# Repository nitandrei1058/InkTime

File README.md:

# InkTime - Smartwatch Open Source

## Diagrama Bloc

```mermaid
graph TD
    subgraph Power Management
        J4[USB-C Connector] -->|VBUS| D3[USBLC6-2SC6Y ESD]
        D3 --> IC1[BQ25180 LiPo Charger]
        BATT[LiPo Battery 250mAh] <--> IC1
        BATT --> U3[MAX17048 Fuel Gauge]
        IC1 -->|VSYS| IC9[RT6160A DC-DC Buck-Boost]
        IC9 -->|3.3V| VDD_SYS[System 3.3V]
    end

    subgraph Microcontroller
        U1[nRF52840 SoC]
        VDD_SYS --> U1
        U1 <-->|SWD| J2[TC2030 Debug]
        U1 <-->|RF| ANT[2.4GHz Antenna]
    end

    subgraph Peripherals
        U1 -->|I2C| IC3[BMA421 IMU]
        U1 -->|I2C| U3
        U1 -->|I2C| IC2[DRV2605L Haptic]
        U1 -->|I2C| IC1
        IC2 --> MOTOR[Vibration Motor]
        U1 -->|SPI + GPIO| J1["EPD Display 1.54 inch"]
        U1 -->|GPIO| BTN[3x Tactile Buttons]
    end
```

## Bill of Materials (BOM)

| Referință | Componentă | Valoare / Pachet | Datasheet | Link JLCParts / Procurare |
|:---|:---|:---|:---|:---|
| **U1** | Nordic nRF52840 | nRF52840-QIAA (QFN-73) | [Datasheet](https://infocenter.nordicsemi.com/pdf/nRF52840_PS_v1.7.pdf) | [C190794](https://jlcpcb.com/partdetail/NordicSemiconductor-nRF52840QIAA/C190794) |
| **IC1** | TI BQ25180 | LiPo Charger (DSBGA-8) | [Datasheet](https://www.ti.com/lit/ds/symlink/bq25180.pdf) | [C3682423](https://jlcpcb.com/partdetail/TexasInstruments-BQ25180YBGR/C3682423) |
| **IC9** | Richtek RT6160A | DC-DC Buck-Boost 3.3V | [Datasheet](https://www.richtek.com/assets/product_file/RT6160A/DS6160A-00.pdf) | [C7065276](https://jlcpcb.com/partdetail/RichtekTech-RT6160AWSC/C7065276) |
| **U3** | Analog MAX17048 | Fuel Gauge (TDFN-8) | [Datasheet](https://www.analog.com/media/en/technical-documentation/data-sheets/MAX17048-MAX17049.pdf) | [C2682616](https://jlcpcb.com/partdetail/2777647-MAX17048GT10/C2682616) |
| **IC3** | Bosch BMA421 | Accelerometru (LGA-12) | [Datasheet](https://www.bosch-sensortec.com/media/boschsensortec/downloads/datasheets/bst-bma423-ds000.pdf) | [C5242966](https://jlcpcb.com/partdetail/BoschSensortec-BMA423/C189517) |
| **IC2** | TI DRV2605L | Haptic Driver (DSBGA) | [Datasheet](https://www.ti.com/lit/ds/symlink/drv2605.pdf) | [C527464](https://jlcpcb.com/partdetail/TexasInstruments-DRV2605YZFR/C81079) |
| **D3** | ST USBLC6-2SC6Y | USB ESD (SOT-23-6) | [Datasheet](https://www.st.com/resource/en/datasheet/usblc6-2.pdf) | [C2969755](https://jlcpcb.com/partdetail/STMicroelectronics-USBLC62SC6Y/C2969755) |
| **J4** | KH-TYPE-C-16P | USB-C 16-pin | - | [C709357](https://jlcpcb.com/partdetail/Shenzhen_KinghelmElec-KH_TYPE_C16P/C709357) |
| **J1** | Molex 503480-2400 | FPC 24-pin pt EPD | [Datasheet](https://www.molex.com/en-us/products/part-detail/503480-2400) | [C122434](https://jlcpcb.com/partdetail/MOLEX-5034802400/C122434) |
| **J2** | TC2030-IDC | SWD Tag-Connect | [Datasheet](https://www.tag-connect.com/product/tc2030-idc-nl) | - |
| **ANT1**| Johanson 2450AT18 | Antenă 2.4GHz | [Datasheet](https://www.johansontechnology.com/datasheets/2450AT18B100E/2450AT18B100E.pdf)| [C2917717](https://jlcpcb.com/partdetail/JohansonDielectrics-2450AT18B100E/C2917717) |
| **X1** | 32MHz | Oscilator HFXO | - | [C383840](https://jlcpcb.com/partdetail/357112-X201632MMB4SI/C383840) |
| **X2** | 32.768kHz | Oscilator LFXO | - | [C32346](https://jlcpcb.com/partdetail/SeikoEpson-Q13FC13500004/C32346) |
| **SW1-3**| EVP-AKE31A | Butoane tactile | [Datasheet](https://industrial.panasonic.com/cdbs/www-data/pdf/ATV0000/ATV0000CE5.pdf) | [C136814](https://jlcpcb.com/parts/componentSearch?searchTxt=EVP-AKE31A) |
| **Q1** | DMG2305UX / AO3401A| P-MOSFET EPD Power | [Datasheet](https://www.diodes.com/assets/Datasheets/DMG2305UX.pdf) | [C15127](https://jlcpcb.com/partdetail/Alpha_OmegaSemicon-AO3401A/C15127) |
| **Q3** | SI1308EDL | N-MOSFET EPD Boost | [Datasheet](https://www.vishay.com/docs/73217/si1308edl.pdf) | [C469327](https://jlcpcb.com/partdetail/VishayIntertech-SI1308EDL_T1GE3/C469327) |
| **-** | AKYGA LP502030 | Baterie LiPo 3.7V / 250mAh | [Datasheet](https://www.tme.eu/Document/b9e12bf26ad0ba929a22ab5d58f022cd/AKY0106.pdf) | Extern |
| **-** | Waveshare 1.54" | Display EPD 200x200 | [Datasheet](https://www.tme.eu/Document/0ca57a8ffbcd57b5bca53252eb9d6ec3/WSH-12561.pdf) | Extern |
| **-** | FIT0774 | Motor Vibrații 10x2.7mm | - | Extern |

*(Notă: Inductoarele de boost/RF/Buck, diodele MBR0530, rezistențele și condensatorii SMD se regăsesc enumerate complet în fișierul `.bom` și `.csv` atașate la proiect).*

## Funcționalitate Hardware

Arhitectura InkTime a fost gândită în primul rând pentru **gestionarea eficientă a consumului de energie** și miniaturizare. Am folosit un proces de asamblare pe o singură parte a plăcii (TOP) și o grosime a PCB-ului de **1mm**.

### 1. Modulul de Procesare & RF
Microcontrollerul central este **Nordic nRF52840 (QFN-73)**, ideal datorită capabilităților extinse, integrarea Bluetooth 5 Low Energy și consum redus. Placa include o antenă de 2.4GHz tip chip (Johanson) conectată la o rețea de adaptare a impedanței formată din condensatori și inductoare minime. Zona de sub antenă respectă o restricție strictă (keepout pe planul de masă) pe ambele straturi pentru a asigura transmisia RF adecvată. Mufa USB-C folosește direct controllerul USB nativ din MCU și este protejată contra descărcărilor electrostatice (ESD) prin componenta D3 (USBLC6).

### 2. Power Management & Încărcare (PMIC)
Sistemul utilizează următoarele blocuri:
*   **BQ25180 (IC1):** Se ocupă de încărcarea celulei LiPo din VBUS (USB-C). Permite configurare hardware via I2C și generează rail-ul de sistem VSYS.
*   **RT6160A (IC9):** Regulator Buck-Boost sincron ce preia tensiunea VSYS/Baterie (3.0V – 4.2V) și oferă un `3.3V` curat pe întreg sistemul (VDD_SYS). E esențial pentru menținerea unei tensiuni stabile când bateria scade sub 3.3V.
*   **MAX17048 (U3):** Fuel Gauge dedicat. Acesta măsoară tensiunea bateriei (State of Charge) și raportează statusul prin I2C. Acest lucru ajută nRF52840 să rămână în deep sleep mai mult timp, omițând folosirea unui ADC intern. Emite alertă fizică prin pinul ALRT.

### 3. Display E-Paper (1.54")
Afișajul comunică cu MCU via **SPI**. Beneficiul E-Paper este consumul zero de curent între refresh-uri. Pentru a tăia chiar și curentul "standby" al panoului, placa conține un circuit separat de gating (Q1, un P-MOSFET) activat prin pinul `EPD_PWR`. De asemenea, pentru că afișajul EPD necesită tensiuni ridicate de refresh, există un circuit boost integrat (Q3 N-MOSFET, bobina de 68uH) pe care MCU îl activează înainte de transmiterea de date SPI.

### 4. Senzori & UI
*   **Accelerometru BMA421 (IC3):** Folosit la monitorizarea numărului de pași (pedometru intern) și detectarea de tilt/mișcare a încheieturii. Comunică I2C și folosește pinii `INT1` și `INT2` pentru a trezi SoC-ul din deep sleep prin intrerupere pe tranzitie (hardware wake).
*   **Feedback Haptic (DRV2605L - IC2):** Rulează pattern-uri haptice dintr-o memorie ROM internă, reducând timpii de procesare ai MCU-ului. Gestionează un motor ERM mic (FIT0774). Poate fi oprit complet din funcționare prin pinul `EN`.
*   **3 Butoane Tactile:** Acționează cu rolurile de Up (`SW_UP`), Enter/Escape (`SW_ENT`) și Down (`SW_DN`). Sunt butoane active-low ce declanșează întreruperi cu rezistențe de pull-up activate din interiorul MCU.

### Calcule Estimative de Consum (Power Budget)
*   **Deep Sleep** (Afișaj static, radio inactiv, RTC + IMU active): **~10 - 20 µA**
*   **BLE Activ** (RX/TX Notificări): **~3 - 5 mA** (burst-uri foarte scurte)
*   **Afișaj E-Paper Refresh** (1 minut): **~10 - 15 mA** (pe durata de ~1s - 2s a refresh-ului parțial)
*   **Alertă Haptică:** **~50 - 100 mA** (timp de fracțiuni de secundă)
Presupunând un profil tipic de ~50 de notificări/zi și refresh o dată pe minut, o baterie de 250mAh ar trebui să dureze cu lejeritate **cel puțin 30 de zile**.

## Mapare Pini nRF52840

Alegerea pinilor a urmărit scurtarea și degajarea traseelor critice de RF, precum și o evadare eficientă din footprint-ul capsulei nRF52840 pe un singur strat de rutare utilitară. 

| Semnal | Pin nRF | Funcție | Detalii & Justificare |
| :--- | :---: | :--- | :--- |
| **I2C_SDA** | `P0.06` | Date I2C | Linii partajate între BMA421, MAX17048, DRV2605 și BQ25180. |
| **I2C_SCL** | `P0.07` | Clock I2C | Linii cu rezistențe pull-up la 3.3V (VDD_SYS). |
| **SPI_MOSI**| `P0.03` | SPI TX | Către J1 (EPD). Folosite pentru trimitere buffer ecran. |
| **SPI_SCK** | `P0.02` | SPI Clock| Către J1 (EPD). |
| **SPI_CS** | `P0.05` | SPI Chip Select | Selecție device SPI (Afișaj). |
| **EPD_DC** | `P0.15` | Data / Command | Controlează modul în care display-ul interpretează payload-ul SPI. |
| **EPD_RST** | `P0.16` | Reset EPD | Resetează starea hardware a panoului E-Paper. |
| **EPD_BUSY**| `P0.17` | BUSY indicator | Pin citit de MCU pentru a pune MCU în delay cât EPD randează frame-ul. |
| **EPD_PWR** | `P1.01` | Enable E-Paper | Deschide tranzistorul MOSFET Q1 pentru a tăia / da power panoului. |
| **IMU_INT1**| `P0.08` | Intrerupere 1 | Primește semnal wake de la accelerometru (gest). |
| **IMU_INT2**| `P1.08` | Intrerupere 2 | Primește semnal pedometru/dublu tap. |
| **PMIC_INT**| `P0.11` | Intrerupere Încărcare| Semnalizează finalizarea încărcării USB. |
| **BAT_ALRT**| `P0.10` | Alertă Baterie | Întrerupere de la fuel gauge la prag de "Low Battery". |
| **HAP_EN** | `P0.12` | DRV2605 Enable | Trezește din deep sleep/shutdown haptic driver-ul IC2. |
| **SW_UP** | `P0.13` | Buton UP | Active Low. |
| **SW_DN** | `P0.14` | Buton DOWN | Active Low. |
| **SW_ENT** | `P1.00` | Buton ENTER | Active Low. |
| **USB_D+** | `P0.20` | USB Data Pozitiv | Rutate direct către protecția ESD și portul J4 (USB nativ în nRF). |
| **USB_D-** | `P0.22` | USB Data Negativ | Rutate direct către protecția ESD și portul J4. |

*Pinii de programare `SWDIO` și `SWDCLK` sunt trași strict la pogo-header-ul Tag-Connect J2 pentru debug.*

## Constrângeri Respectate & Design Log
*   **Plasamentul 100% TOP:** Placa a fost rutată cu absolut toate componentele plasate exclusiv pe fața de TOP. Acest lucru garantează o grosime asamblată cât mai subțire (având spatele PCB-ului liber pentru lipirea fixă a bateriei), menținându-se într-o grosime maximă de **1mm** a PCB-ului.
*   **Erori DRC Asumate (Mecanic):** Mufa USB-C (J4) și cele 3 butoane tactile au fost amplasate strategic pentru a se potrivi exact cu decupajele din carcasa smartwatch-ului. Această poziționare generează erori de "Dimension" / "Clearance" la marginea plăcii în DRC, pe care mi le-am asumat.
*   **Erori DRC Asumate (Via in Pad):** Datorită densității pachetului aQFN73 al nRF52840, evadarea tuturor semnalelor pe un număr limitat de straturi a necesitat utilizarea de vias direct în pad-uri ("drill in pad") pentru pinii altfel inaccesibili. Erorile DRC rezultate din această tehnică de rutare sunt asumate.
*   **Cerințe layout RF:** Pentru antena 2450AT18 s-a menținut decupajul recomandat pe toate planurile de masă, interzicând ruta semnalelor de date/putere sub zona antenei pentru a optimiza eficiența și a reduce EMI.

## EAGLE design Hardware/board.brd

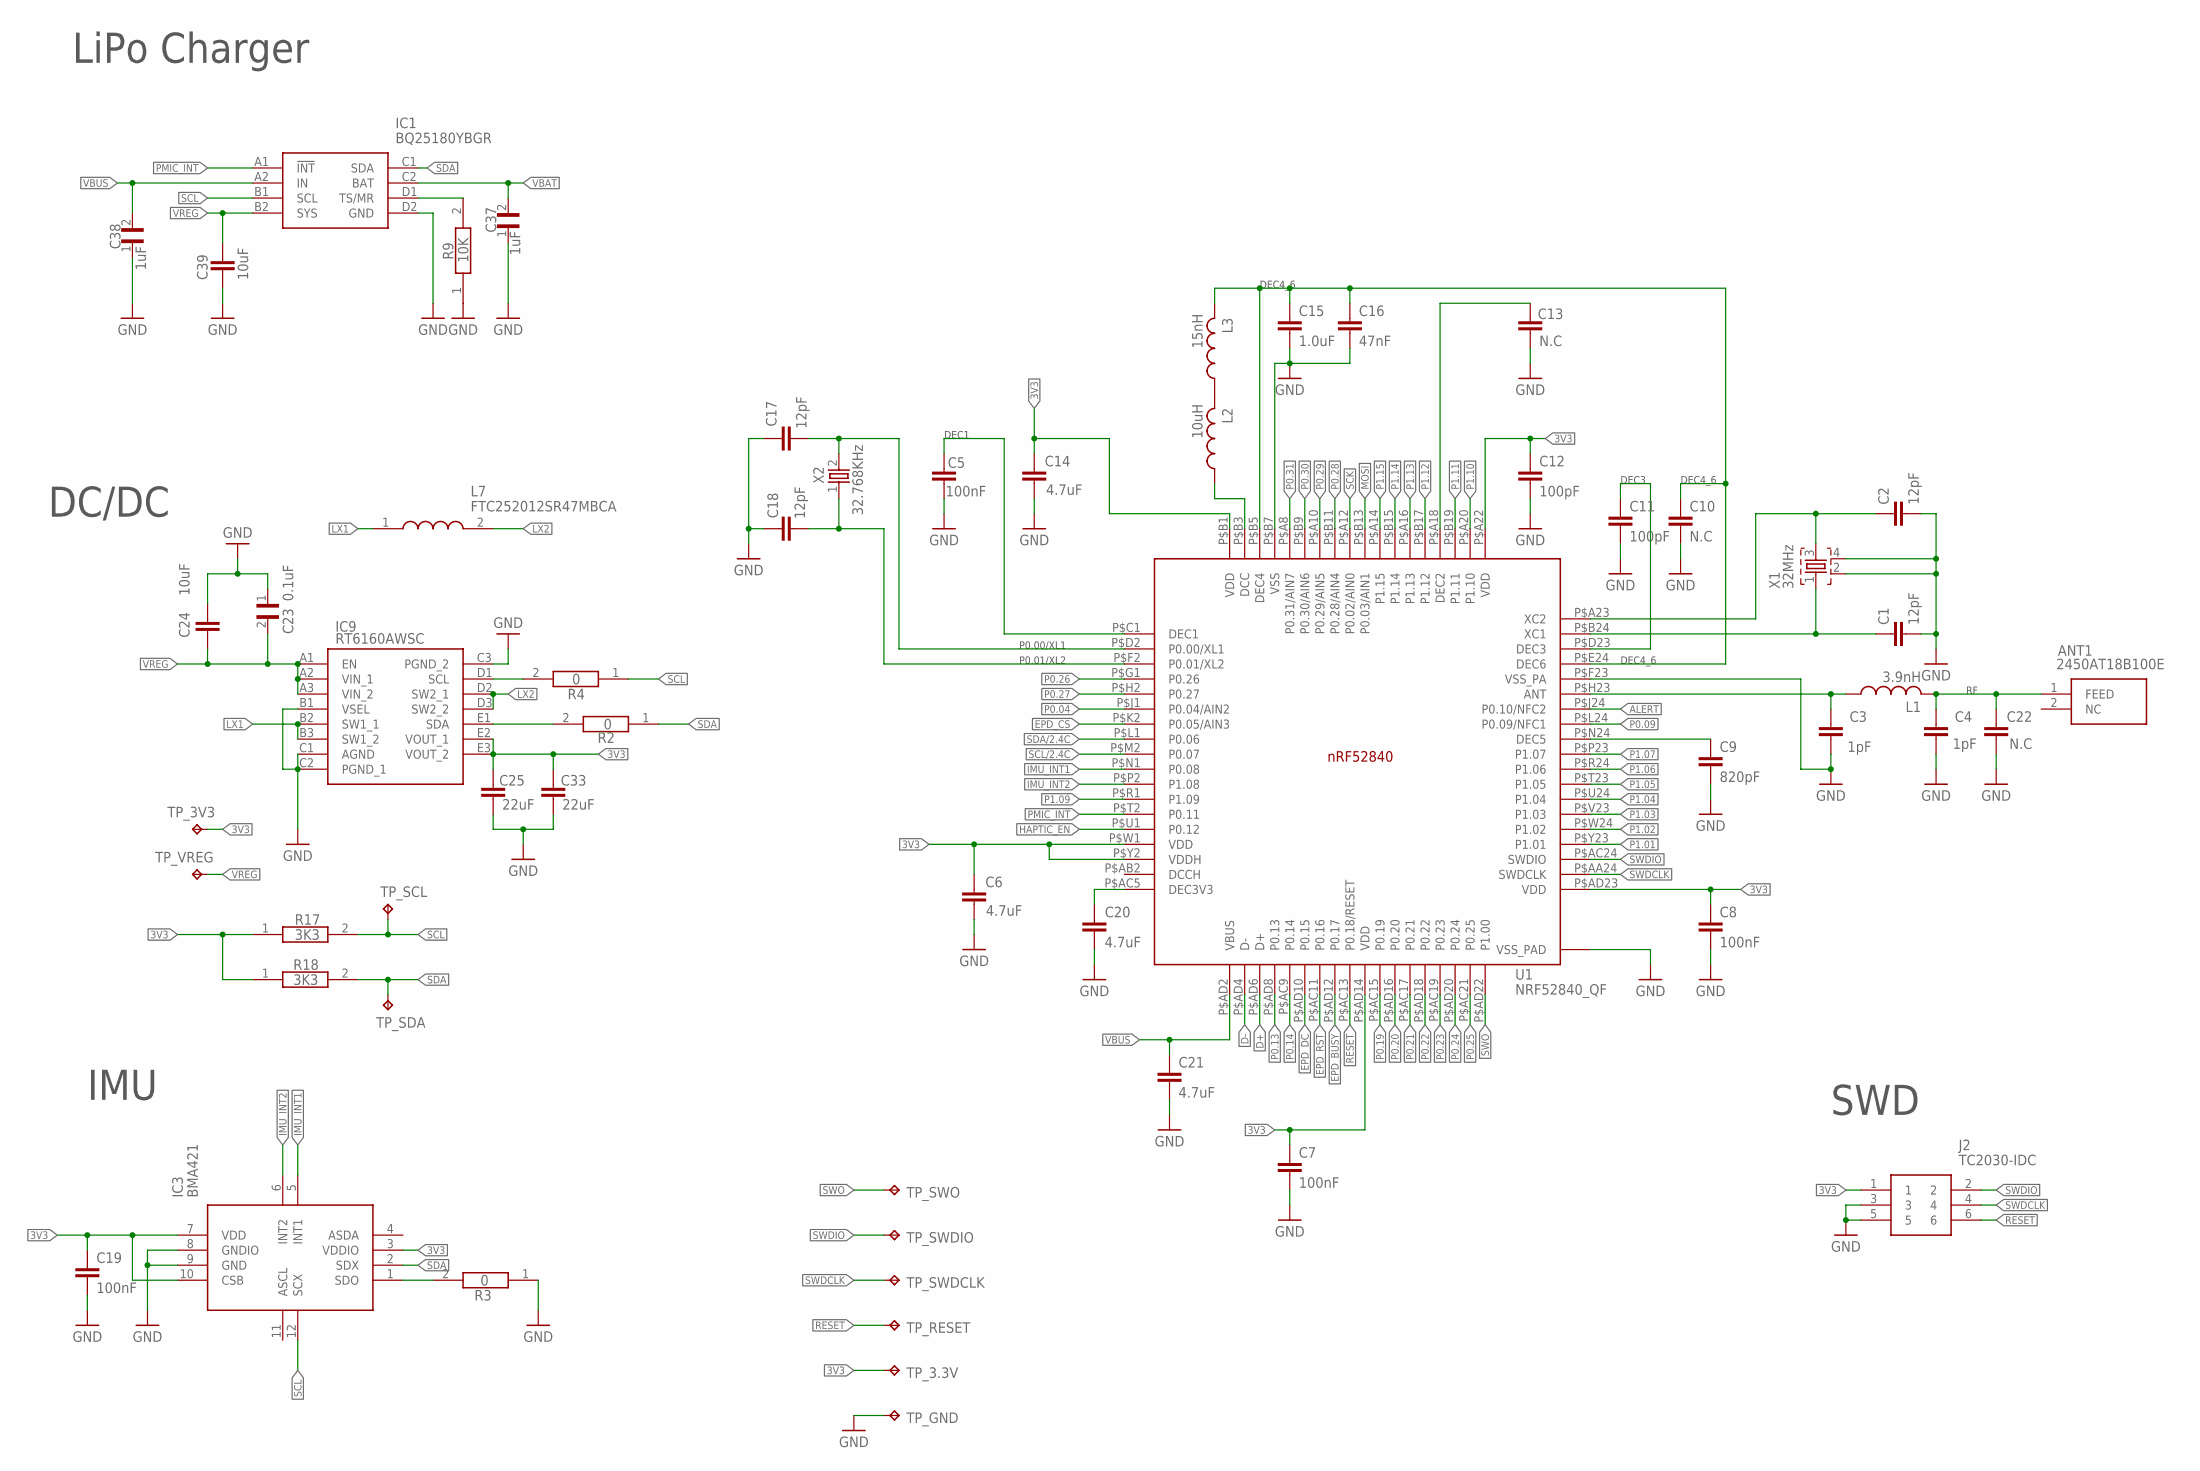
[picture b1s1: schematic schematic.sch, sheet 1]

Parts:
ANT1: 2450AT18B100E; 2450AT18B100E_ANTC3216X140N
C1, C2, C17, C18: 12pF; NORDIC_NRF_3_RESC0201_L
C3, C4: 1pF; NORDIC_NRF_3_RESC0201_L
C5, C7, C8, C19: 100nF; NORDIC_NRF_3_RESC0201_L
C6, C14, C20, C21: 4.7uF; NORDIC_NRF_3_RESC0402_L
C9: 820pF; NORDIC_NRF_3_RESC0201_L
C10, C13, C22: N.C; NORDIC_NRF_3_RESC0201_L
C11, C12: 100pF; NORDIC_NRF_3_RESC0201_L
C15: 1.0uF; NORDIC_NRF_3_RESC0402_L
C16: 47nF; NORDIC_NRF_3_RESC0201_L
C23: 0.1uF; GRM011R60J152KE01L_2_CAPC0201X13N
C24, C39: 10uF; NORDIC_NRF_3_RESC0402_L
C25, C33: 22uF; NORDIC_NRF_3_RESC0402_L
C37, C38: 1uF; GRM011R60J152KE01L_2_CAPC0201X13N
IC1: BQ25180YBGR; BQ25180YBGR_BGA8C40P2X4_100X155X50
IC3: BMA421; BMA423_BMA423
IC9: RT6160AWSC; RT6160AWSC_BGA15C40P3X5_140X230X60
J2: TC2030-IDC; TC2030-IDC_TC2030IDC
L1: 3.9nH; NORDIC_NRF_2_RESC0402_M
L2: 10uH; NORDIC_NRF_2_RESC0603_L
L3: 15nH; NORDIC_NRF_2_RESC0201_L
L7: FTC252012SR47MBCA; MLP2016SR47MT0S1_INDC2016X100N
R2, R3, R4: 0; CPF0201D7K68C1_0201
R9: 10K; CPF0201D7K68C1_0201
R17, R18: 3K3; CPF0201D7K68C1_0201
TP_3.3V, TP_3V3: HECTOR_WATCH_1_TPTP20R; HECTOR_WATCH_1_TP20R
TP_GND: HECTOR_WATCH_1_TPTP20R; HECTOR_WATCH_1_TP20R
TP_RESET: HECTOR_WATCH_1_TPTP20R; HECTOR_WATCH_1_TP20R
TP_SCL: HECTOR_WATCH_1_TPTP20R; HECTOR_WATCH_1_TP20R
TP_SDA: HECTOR_WATCH_1_TPTP20R; HECTOR_WATCH_1_TP20R
TP_SWDCLK: HECTOR_WATCH_1_TPTP20R; HECTOR_WATCH_1_TP20R
TP_SWDIO: HECTOR_WATCH_1_TPTP20R; HECTOR_WATCH_1_TP20R
TP_SWO: HECTOR_WATCH_1_TPTP20R; HECTOR_WATCH_1_TP20R
TP_VREG: HECTOR_WATCH_1_TPTP20R; HECTOR_WATCH_1_TP20R
U1: NRF52840_QF; NORDIC_NRF_4_AQFN50P700X700X85_HS-74N
X1: 32MHz; NORDIC_NRF_BT-XTAL_2016_N
X2: 32.768KHz; NORDIC_NRF_1_XTAL_3215_N

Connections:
3V3: C6.2, C7.1, C8.1, C12.1, C14.2, C19.1, C25.1, C33.1, IC3.3 (VDDIO), IC3.7 (VDD), IC3.10 (CSB), IC9.E2 (VOUT_1), IC9.E3 (VOUT_2), J2.1, R17.1, R18.1, TP_3.3V.TP, TP_3V3.TP, U1.P$A22 (VDD), U1.P$AD14 (VDD), U1.P$AD23 (VDD), U1.P$B1 (VDD), U1.P$W1 (VDD), U1.P$Y2 (VDDH); also elsewhere on the board
ALERT: U1.P$J24 (P0.10/NFC2); also elsewhere on the board
D+: U1.P$AD6 (D+); also elsewhere on the board
D-: U1.P$AD4 (D-); also elsewhere on the board
EPD_BUSY: U1.P$AD12 (P0.17); also elsewhere on the board
EPD_CS: U1.P$K2 (P0.05/AIN3); also elsewhere on the board
EPD_DC: U1.P$AD10 (P0.15); also elsewhere on the board
EPD_RST: U1.P$AC11 (P0.16); also elsewhere on the board
GND: C1.2, C2.2, C3.1, C4.1, C5.1, C6.1, C7.2, C8.2, C9.2, C10.2, C11.2, C12.2, C13.2, C14.1, C15.2, C16.2, C17.2, C18.2, C19.2, C20.1, C21.2, C22.1, C23.1, C24.1, C25.2, C33.2, C37.1, C38.1, C39.2, IC1.D2 (GND), IC3.8 (GNDIO), IC3.9 (GND), IC9.B1 (VSEL), IC9.C1 (AGND), IC9.C2 (PGND_1), IC9.C3 (PGND_2), J2.3, J2.5, R3.1, R9.1, TP_GND.TP, U1.P$74 (VSS_PAD), U1.P$75 (VSS_PAD), U1.P$76 (VSS_PAD), U1.P$77 (VSS_PAD), U1.P$78 (VSS_PAD), U1.P$79 (VSS_PAD), U1.P$80 (VSS_PAD), U1.P$81 (VSS_PAD), U1.P$82 (VSS_PAD), U1.P$83 (VSS_PAD), U1.P$84 (VSS_PAD), U1.P$85 (VSS_PAD), U1.P$86 (VSS_PAD), U1.P$87 (VSS_PAD), U1.P$88 (VSS_PAD), U1.P$89 (VSS_PAD), U1.P$90 (VSS_PAD), U1.P$B7 (VSS), U1.P$F23 (VSS_PA), X1.2, X1.4; also elsewhere on the board
HAPTIC_EN: U1.P$U1 (P0.12); also elsewhere on the board
IMU_INT1: IC3.5 (INT1), U1.P$N1 (P0.08)
IMU_INT2: IC3.6 (INT2), U1.P$P2 (P1.08)
LX1: IC9.B2 (SW1_1), IC9.B3 (SW1_2), L7.1
LX2: IC9.D2 (SW2_1), IC9.D3 (SW2_2), L7.2
MOSI: U1.P$B13 (P0.03/AIN1); also elsewhere on the board
unnamed: IC1.D1 (TS/MR), R9.2
unnamed: C9.1, U1.P$N24 (DEC5)
unnamed: C3.2, L1.1, U1.P$H23 (ANT)
unnamed: IC9.D1 (SCL), R4.2
unnamed: IC9.E1 (SDA), R2.2
unnamed: C20.2, U1.P$AC5 (DEC3V3)
unnamed: ANT1.1 (FEED), C4.2, C22.2, L1.2
unnamed: C1.1, U1.P$B24 (XC1), X1.1
unnamed: C2.1, U1.P$A23 (XC2), X1.3
unnamed: C11.1, U1.P$D23 (DEC3)
unnamed: C18.1, U1.P$F2 (P0.01/XL2), X2.1
unnamed: C13.1, U1.P$A18 (DEC2)
unnamed: L2.1, L3.2
unnamed: L2.2, U1.P$B3 (DCC)
unnamed: C10.1, C15.1, C16.1, L3.1, U1.P$B5 (DEC4), U1.P$E24 (DEC6)
unnamed: C17.1, U1.P$D2 (P0.00/XL1), X2.2
unnamed: IC3.1 (SDO), R3.2
unnamed: C5.2, U1.P$C1 (DEC1)
P0.04: U1.P$J1 (P0.04/AIN2)
P0.09: U1.P$L24 (P0.09/NFC1)
P0.13: U1.P$AD8 (P0.13); also elsewhere on the board
P0.14: U1.P$AC9 (P0.14); also elsewhere on the board
P0.19: U1.P$AC15 (P0.19)
P0.20: U1.P$AD16 (P0.20)
P0.21: U1.P$AC17 (P0.21)
P0.22: U1.P$AD18 (P0.22)
P0.23: U1.P$AC19 (P0.23)
P0.24: U1.P$AD20 (P0.24)
P0.25: U1.P$AC21 (P0.25)
P0.26: U1.P$G1 (P0.26)
P0.27: U1.P$H2 (P0.27)
P0.28: U1.P$B11 (P0.28/AIN4)
P0.29: U1.P$A10 (P0.29/AIN5)
P0.30: U1.P$B9 (P0.30/AIN6)
P0.31: U1.P$A8 (P0.31/AIN7)
P1.01: U1.P$Y23 (P1.01); also elsewhere on the board
P1.02: U1.P$W24 (P1.02); also elsewhere on the board
P1.03: U1.P$V23 (P1.03)
P1.04: U1.P$U24 (P1.04)
P1.05: U1.P$T23 (P1.05)
P1.06: U1.P$R24 (P1.06)
P1.07: U1.P$P23 (P1.07)
P1.09: U1.P$R1 (P1.09)
P1.10: U1.P$A20 (P1.10)
P1.11: U1.P$B19 (P1.11)
P1.12: U1.P$B17 (P1.12)
P1.13: U1.P$A16 (P1.13)
P1.14: U1.P$B15 (P1.14)
P1.15: U1.P$A14 (P1.15)
PMIC_INT: IC1.A1 (!INT), U1.P$T2 (P0.11)
RESET: J2.6, TP_RESET.TP, U1.P$AC13 (P0.18/RESET)
SCK: U1.P$A12 (P0.02/AIN0); also elsewhere on the board
SWDCLK: J2.4, TP_SWDCLK.TP, U1.P$AA24 (SWDCLK)
SWDIO: J2.2, TP_SWDIO.TP, U1.P$AC24 (SWDIO)
SWO: TP_SWO.TP, U1.P$AD22 (P1.00)
VBUS: C21.1, C38.2, IC1.A2 (IN), U1.P$AD2 (VBUS); also elsewhere on the board
VREG: C23.2, C24.2, C39.1, IC1.B2 (SYS), IC9.A1 (EN), IC9.A2 (VIN_1), IC9.A3 (VIN_2), TP_VREG.TP

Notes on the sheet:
LiPo Charger
DC/DC
IMU
SWD
DEC1
DEC4_6
DEC3
P0.00/XL1
P0.01/XL2

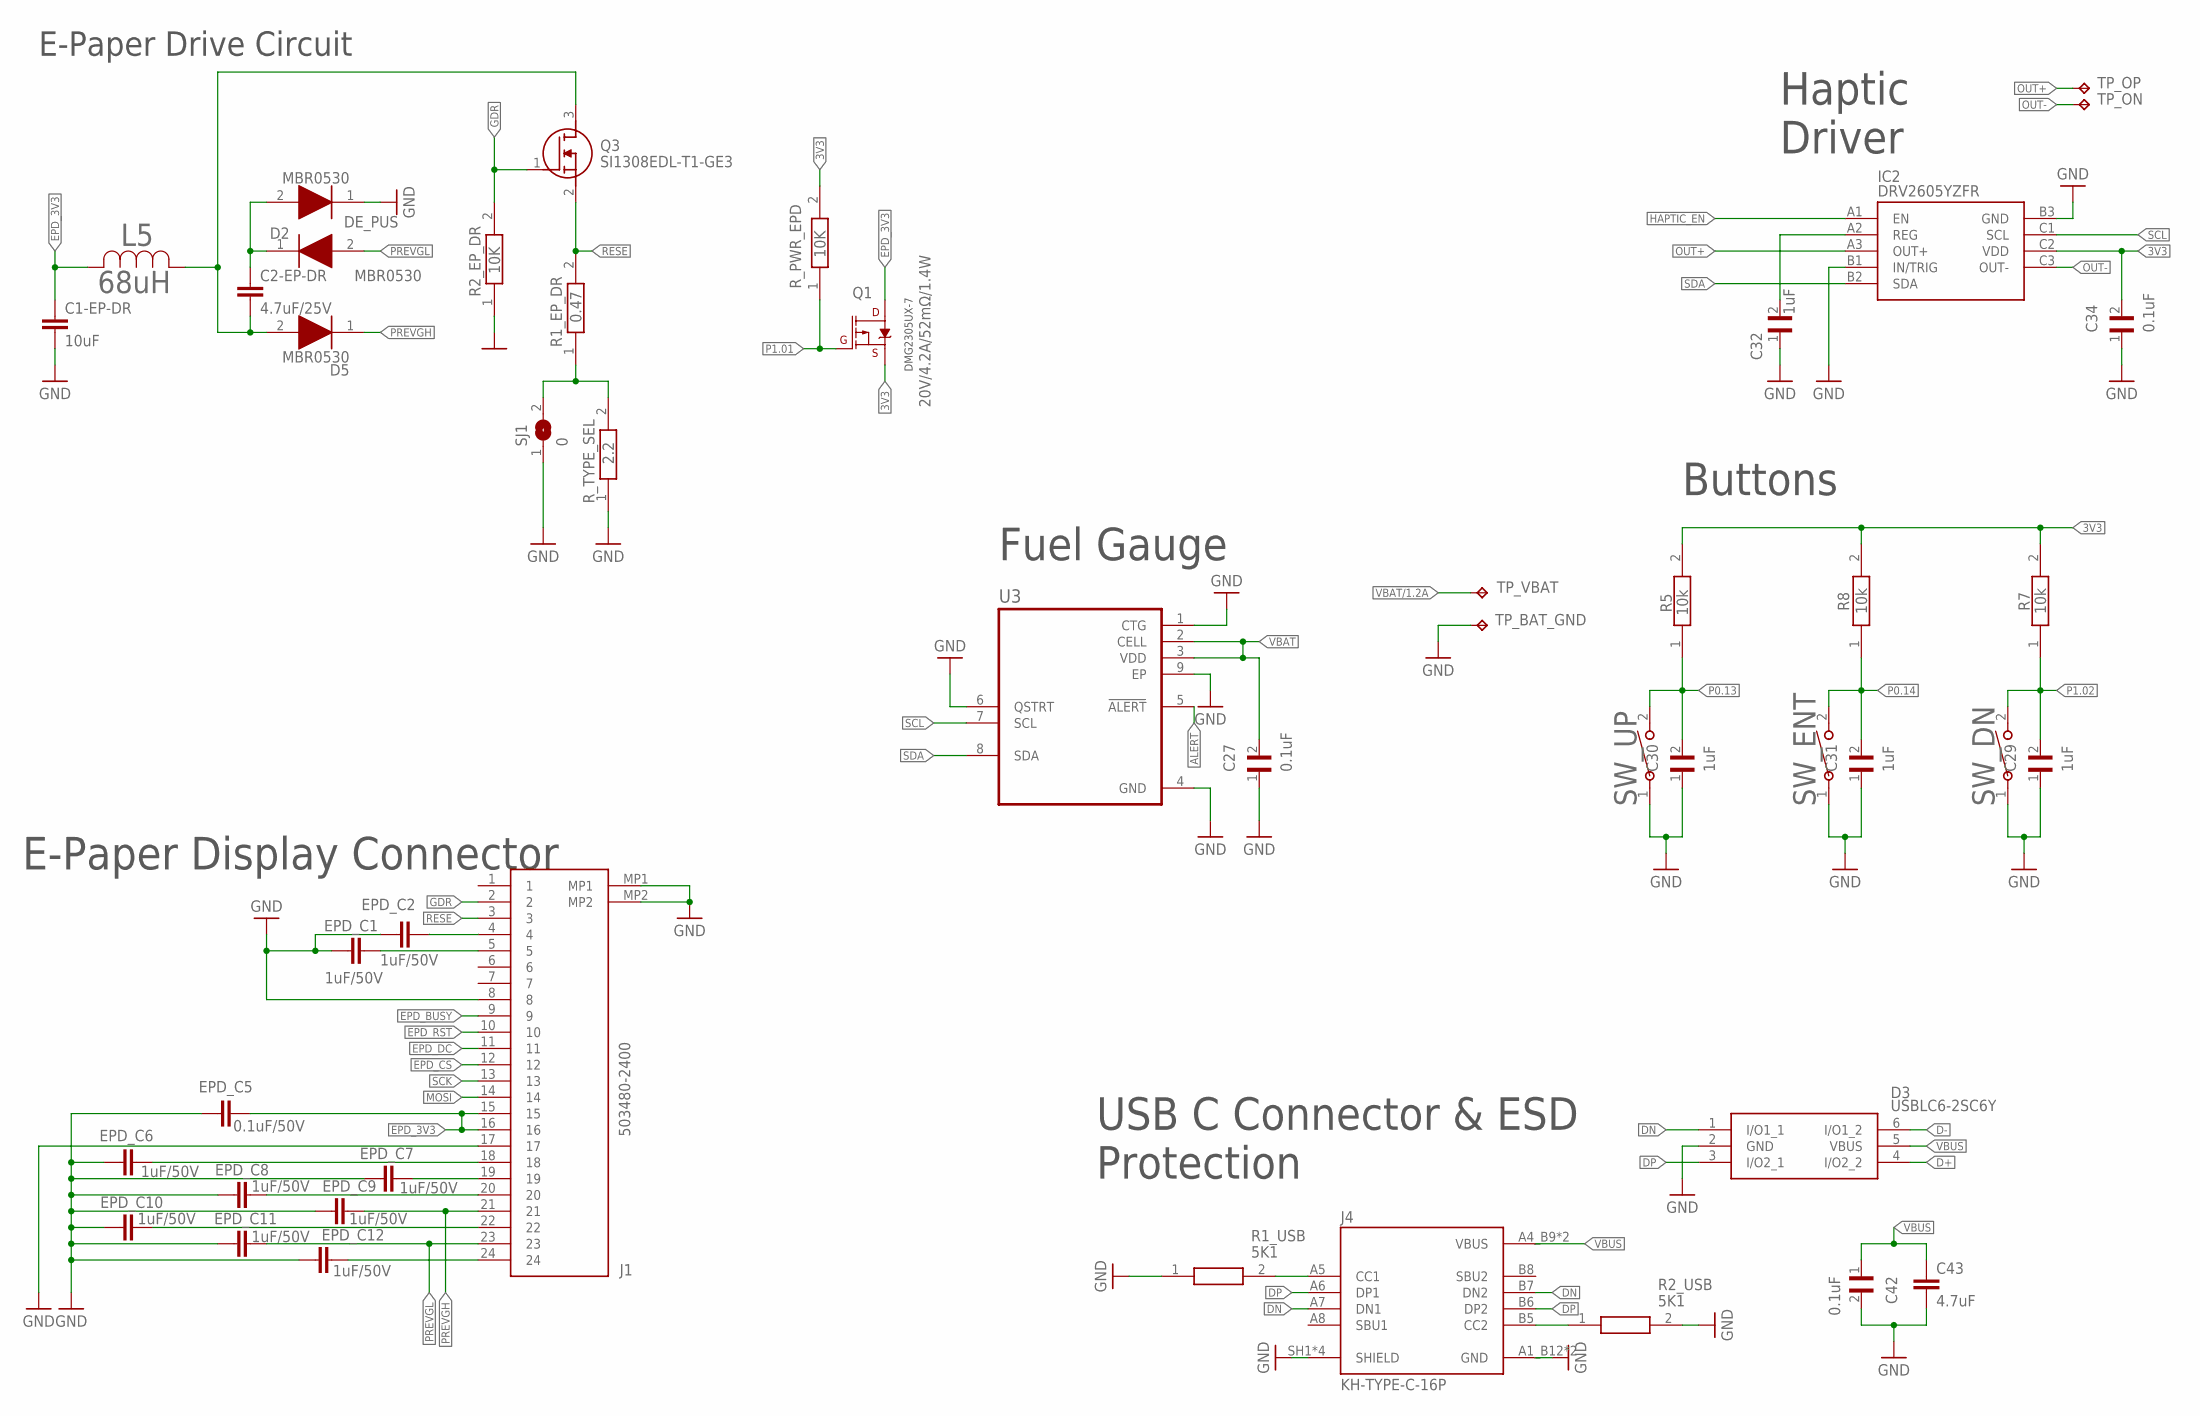
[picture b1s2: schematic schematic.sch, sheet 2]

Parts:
C1-EP-DR: 10uF; NORDIC_NRF_3_RESC0402_L
C2-EP-DR: 4.7uF/25V; NORDIC_NRF_3_RESC0402_L
C27, C34, C42: 0.1uF; GRM011R60J152KE01L_2_CAPC0201X13N
C29, C30, C31, C32: 1uF; GRM011R60J152KE01L_2_CAPC0201X13N
C43: 4.7uF; NORDIC_NRF_3_RESC0402_L
D2, D5: MBR0530; ESP32_C6_LIBRARY_5_SOD3716X135N
D3: USBLC6-2SC6Y; ESP32_C6_LIBRARY_3_SOT95P280X145-6N
DE_PUS: MBR0530; ESP32_C6_LIBRARY_5_SOD3716X135N
EPD_C1, EPD_C2, EPD_C6, EPD_C7, EPD_C8, EPD_C9, EPD_C10, EPD_C11, EPD_C12: 1uF/50V; NORDIC_NRF_3_RESC0402_L
EPD_C5: 0.1uF/50V; NORDIC_NRF_3_RESC0402_L
IC2: DRV2605YZFR; DRV2605YZFR_BGA9C50P3X3_144X144X62
J1: 503480-2400; 503480-2400_5034802400
J4: KH-TYPE-C-16P; KH-TYPE-C-16P_KINGHELM_KH-TYPE-C-16P
L5: 68uH; ESP32_C6_LIBRARY_2_IND_4828-WE-TPC_WRE
Q1: 20V/4.2A/52mΩ/1.4W; ESP32_C6_LIBRARY_4_ESP32_C6_LIBRARY_4_ESP32_C6_LIBRARY_4_ES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
Q3: SI1308EDL-T1-GE3; ESP32_C6_LIBRARY_6_SOT65P210X110-3N
R1_EP_DR: 0.47; CPF0201D7K68C1_0201
R1_USB, R2_USB: 5K1; CPF0201D7K68C1_0201
R2_EP_DR: 10K; CPF0201D7K68C1_0201
R5, R7, R8: 10k; CPF0201D7K68C1_0201
R_PWR_EPD: 10K; CPF0201D7K68C1_0201
R_TYPE_SEL: 2.2; CPF0201D7K68C1_0201
SJ1: 0; ESP32_C6_LIBRARY_7_JUMPER_SJ
SW_DN: 2025-10-22_07-23-44_LIBRARY_EVP-AKE31ASW_EVP-AKE3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; 2025-10-22_07-23-44_LIBRARY_SW_EVP-AKE31A_PAN
SW_ENT: 2025-10-22_07-23-44_LIBRARY_EVP-AKE31ASW_EVP-AKE3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; 2025-10-22_07-23-44_LIBRARY_SW_EVP-AKE31A_PAN
SW_UP: 2025-10-22_07-23-44_LIBRARY_EVP-AKE31ASW_EVP-AKE3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; 2025-10-22_07-23-44_LIBRARY_SW_EVP-AKE31A_PAN
TP_BAT_GND: HECTOR_WATCH_1_TPTP20R; HECTOR_WATCH_1_TP20R
TP_ON: HECTOR_WATCH_1_TPTP20R; HECTOR_WATCH_1_TP20R
TP_OP: HECTOR_WATCH_1_TPTP20R; HECTOR_WATCH_1_TP20R
TP_VBAT: HECTOR_WATCH_1_TPTP20R; HECTOR_WATCH_1_TP20R
U3: ESP32_C6_LIBRARY_MAX17048G+T10; ESP32_C6_LIBRARY_SON50P200X200X80-9N

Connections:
3V3: C34.2, IC2.C2 (VDD), Q1.2 (S), R5.2, R7.2, R8.2, R_PWR_EPD.2; also elsewhere on the board
ALERT: U3.5 (!ALERT); also elsewhere on the board
D+: D3.4 (I/O2_2); also elsewhere on the board
D-: D3.6 (I/O1_2); also elsewhere on the board
DN: D3.1 (I/O1_1), J4.A7 (DN1), J4.B7 (DN2)
DP: D3.3 (I/O2_1), J4.A6 (DP1), J4.B6 (DP2)
EPD_3V3: C1-EP-DR.1, EPD_C5.2, J1.15, J1.16, L5.2, Q1.3 (D)
EPD_BUSY: J1.9; also elsewhere on the board
EPD_CS: J1.12; also elsewhere on the board
EPD_DC: J1.11; also elsewhere on the board
EPD_RST: J1.10; also elsewhere on the board
GDR: J1.2, Q3.1 (G), R2_EP_DR.2
GND: C1-EP-DR.2, C27.1, C29.1, C30.1, C31.1, C32.1, C34.1, C42.2, C43.2, D3.2 (GND), DE_PUS.1 (K), EPD_C1.1, EPD_C2.1, EPD_C5.1, EPD_C6.1, EPD_C7.1, EPD_C8.1, EPD_C9.1, EPD_C10.1, EPD_C11.1, EPD_C12.1, IC2.B1 (IN/TRIG), IC2.B3 (GND), J1.8, J1.17, J1.MP1, J1.MP2, J4.A1_B12 (GND), J4.A12_B1 (GND), J4.SH1 (SHIELD), J4.SH2 (SHIELD), J4.SH3 (SHIELD), J4.SH4 (SHIELD), R1_USB.1, R2_EP_DR.1, R2_USB.2, R_TYPE_SEL.1, SJ1.1, SW_DN.1, SW_ENT.1, SW_UP.1, TP_BAT_GND.TP, U3.1 (CTG), U3.4 (GND), U3.6 (QSTRT), U3.9 (EP); also elsewhere on the board
HAPTIC_EN: IC2.A1 (EN); also elsewhere on the board
MOSI: J1.14; also elsewhere on the board
unnamed: R1_EP_DR.1, R_TYPE_SEL.2, SJ1.2
unnamed: C32.2, IC2.A2 (REG)
unnamed: C2-EP-DR.1, D2.1 (K), DE_PUS.2 (A)
unnamed: C2-EP-DR.2, D5.2 (A), L5.1, Q3.3 (D)
unnamed: EPD_C2.2, J1.4
unnamed: EPD_C1.2, J1.5
unnamed: J4.B5 (CC2), R2_USB.1
unnamed: EPD_C7.2, J1.19
unnamed: EPD_C12.2, J1.24
unnamed: EPD_C6.2, J1.18
unnamed: EPD_C8.2, J1.20
unnamed: EPD_C10.2, J1.22
unnamed: J4.A5 (CC1), R1_USB.2
OUT+: IC2.A3 (OUT+), TP_OP.TP
OUT-: IC2.C3 (OUT-), TP_ON.TP
P0.13: C30.2, R5.1, SW_UP.2; also elsewhere on the board
P0.14: C31.2, R8.1, SW_ENT.2; also elsewhere on the board
P1.01: Q1.1 (G), R_PWR_EPD.1; also elsewhere on the board
P1.02: C29.2, R7.1, SW_DN.2; also elsewhere on the board
PREVGH: D5.1 (K), EPD_C9.2, J1.21
PREVGL: D2.2 (A), EPD_C11.2, J1.23
RESE: J1.3, Q3.2 (S), R1_EP_DR.2
SCK: J1.13; also elsewhere on the board
VBUS: C42.1, C43.1, D3.5 (VBUS), J4.A4_B9 (VBUS), J4.A9_B4 (VBUS); also elsewhere on the board

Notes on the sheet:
E-Paper Drive Circuit
DMG2305UX-7
Haptic Driver
Fuel Gauge
Buttons
USB C Connector & ESD Protection
E-Paper Display Connector

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
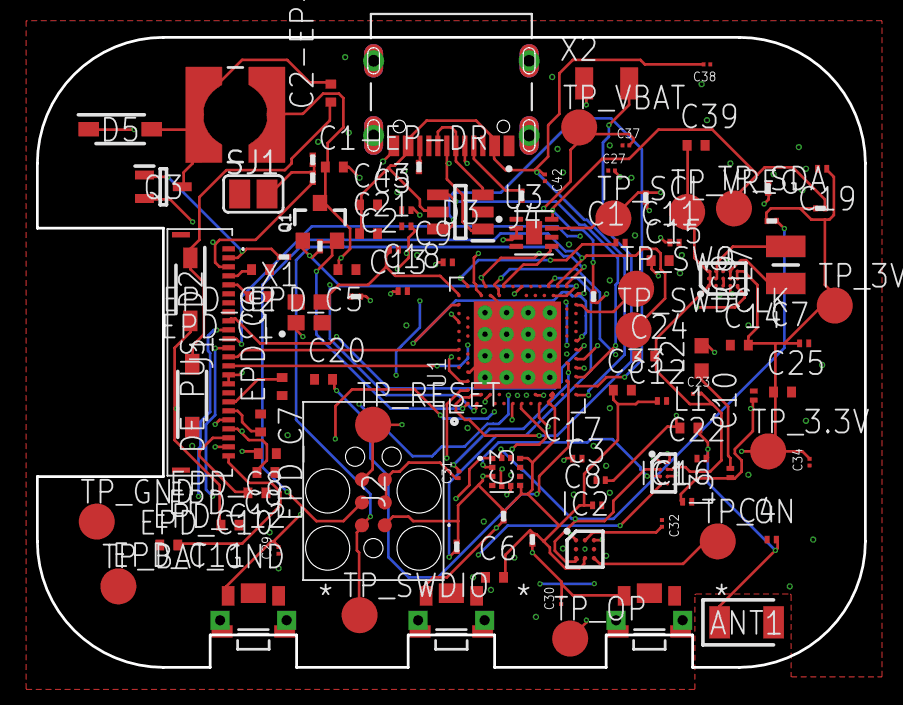
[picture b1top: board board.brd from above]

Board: 4 copper layers, 46.0 x 35.0 mm, 105 parts (0 on the bottom side), 70 nets.

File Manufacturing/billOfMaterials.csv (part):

Reference Designators;Quantity;Description;Package;Value;Manufacturer;Manufacturer Part Number;Vendor;Vendor Part Number;Top/Bottom;ARROW_PART_NUMBER;ARROW_PRICE-STOCK;AVAILABILITY;CHECK_PRICES;COPYRIGHT;DESCRIPTION;JLCPCB;MANUFACTURER_NAME;MANUFACTURER_PART_NUMBER;MF;MFR_NAME;MOUSER_PART_NUMBER;MOUSER_PRICE-STOCK;MP;PACKAGE;POPULARITY;PRICE;PROD_ID;PURCHASE-URL;SNAPEDA_LINK;TP_SIGNAL_NAME;
;1;Board;Board;;;;;;;;;;;;;;;;;;;;;;;;;;;;
ANT1;1;Antennas 2.45GHz ANTENNA;2450AT18B100E_ANTC3216X140N;2450AT18B100E;;;;;Top;2450AT18B100E;https://www.arrow.com/en/products/2450at18b100e/johanson-die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;;;;Antennas 2.45GHz ANTENNA;;JOHANSON TECHNOLOGY;2450AT18B100E;;;609-2450AT18B100E;https://www.mouser.co.uk/ProductDetail/Johanson-Technology/2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;;;;;;;;;
C1, C2, C17, C18;4;Generic chip capacitor;NORDIC_NRF_3_RESC0201_L;12pF;;;;;Top;;;;;;;;;;;;;;;;;;;;;;
C1-EP-DR, C24, C39;3;Generic chip capacitor;NORDIC_NRF_3_RESC0402_L;10uF;;;;;Top;;;;;;;;;;;;;;;;;;;;;;
C2-EP-DR;1;Generic chip capacitor;NORDIC_NRF_3_RESC0402_L;4.7uF/25V;;;;;Top;;;;;;;;;;;;;;;;;;;;;;
C3, C4;2;Generic chip capacitor;NORDIC_NRF_3_RESC0201_L;1pF;;;;;Top;;;;;;;;;;;;;;;;;;;;;;
C5, C7, C8, C19;4;Generic chip capacitor;NORDIC_NRF_3_RESC0201_L;100nF;;;;;Top;;;;;;;;;;;;;;;;;;;;;;
C6, C14, C20, C21, C43;5;Generic chip capacitor;NORDIC_NRF_3_RESC0402_L;4.7uF;;;;;Top;;;;;;;;;;;;;;;;;;;;;;
C9;1;Generic chip capacitor;NORDIC_NRF_3_RESC0201_L;820pF;;;;;Top;;;;;;;;;;;;;;;;;;;;;;
C10, C13, C22;3;Generic chip capacitor;NORDIC_NRF_3_RESC0201_L;N.C;;;;;Top;;;;;;;;;;;;;;;;;;;;;;
C11, C12;2;Generic chip capacitor;NORDIC_NRF_3_RESC0201_L;100pF;;;;;Top;;;;;;;;;;;;;;;;;;;;;;
C15;1;Generic chip capacitor;NORDIC_NRF_3_RESC0402_L;1.0uF;;;;;Top;;;;;;;;;;;;;;;;;;;;;;
C16;1;Generic chip capacitor;NORDIC_NRF_3_RESC0201_L;47nF;;;;;Top;;;;;;;;;;;;;;;;;;;;;;
C23, C27, C34, C42;4;Check availability;GRM011R60J152KE01L_2_CAPC0201X13N;0.1uF;;;;;Top;;;In Stock;https://www.snapeda.com/parts/GRM011R60J152KE01L/Murata/view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;;                                                      SMD Capacitor X5R(EIA) with Capacitance: 1500pF Tol. 10%. Rated Voltage: 6.3Vdc                                              ;;;;Murata;;;;GRM011R60J152KE01L;0201 Murata;;None;;;https://www.snapeda.com/parts/GRM011R60J152KE01L/Murata/view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;;
C25, C33;2;Generic chip capacitor;NORDIC_NRF_3_RESC0402_L;22uF;;;;;Top;;;;;;;;;;;;;;;;;;;;;;
C29, C30, C31, C32, C37, C38;6;Check availability;GRM011R60J152KE01L_2_CAPC0201X13N;1uF;;;;;Top;;;In Stock;https://www.snapeda.com/parts/GRM011R60J152KE01L/Murata/view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;;                                                      SMD Capacitor X5R(EIA) with Capacitance: 1500pF Tol. 10%. Rated Voltage: 6.3Vdc                                              ;;;;Murata;;;;GRM011R60J152KE01L;0201 Murata;;None;;;https://www.snapeda.com/parts/GRM011R60J152KE01L/Murata/view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;;
D2, D5, DE_PUS;3;ON SEMICONDUCTOR - MBR0530 - DIODE, SCHOTTKY, 0.5A, 30V, SOD-123;ESP32_C6_LIBRARY_5_SOD3716X135N;MBR0530;;;;;Top;;;In Stock;https://www.snapeda.com/parts/MBR0530/Onsemi/view-part/?ref=eda;; Diode Schottky 30 V 500mA Surface Mount SOD-123 ;;;;ON Semiconductor;;;;MBR0530;SOD-123-2 ON Semiconductor;;None;;https://www.snapeda.com/api/url_track_click_mouser/?unipart_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 Semiconductor&part_name=MBR0530&search_term=None;https://www.snapeda.com/parts/MBR0530/Onsemi/view-part/?ref=snap;;
D3;1;Low Cap. ESD Protection Auto SOT-23-6 STMicroelectronics USBLC6-2SC6Y, Dual Uni-Directional TVS Diode Array, 6-Pin SOT-23;ESP32_C6_LIBRARY_3_SOT95P280X145-6N;USBLC6-2SC6Y;;;;;Top;;;In Stock;https://www.snapeda.com/parts/USBLC6-2SC6Y/STMicroelectronic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;; 17V Clamp 5A (8/20µs) Ipp Tvs Diode Surface Mount SOT-23-6 ;;;;STMicroelectronics;;;;USBLC6-2SC6Y;SOT-23-6 STMicroelectronics;;None;;;https://www.snapeda.com/parts/USBLC6-2SC6Y/STMicroelectronic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;;
EPD_C1, EPD_C2, EPD_C6, EPD_C7, EPD_C8, EPD_C9, EPD_C10, EPD_C11, EPD_C12;9;Generic chip capacitor;NORDIC_NRF_3_RESC0402_L;1uF/50V;;;;;Top;;;;;;;;;;;;;;;;;;;;;;
EPD_C5;1;Generic chip capacitor;NORDIC_NRF_3_RESC0402_L;0.1uF/50V;;;;;Top;;;;;;;;;;;;;;;;;;;;;;
IC1;1;Charger IC Lithium Ion/Polymer, Lithium Iron Phosphate 8-DSBGA (1.6x1.1);BQ25180YBGR_BGA8C40P2X4_100X155X50;BQ25180YBGR;;;;;Top;BQ25180YBGR;https://www.arrow.com/en/products/bq25180ybgr/texas-instrume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;;;;Charger IC Lithium Ion/Polymer, Lithium Iron Phosphate 8-DSBGA (1.6x1.1);;Texas Instruments;BQ25180YBGR;;;595-BQ25180YBGR;https://www.mouser.co.uk/ProductDetail/Texas-Instruments/BQ2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;;;;;;;;;
IC2;1;Haptic Driver for ERM/LRA with Built-In Library and Smart Loop Architecture;DRV2605YZFR_BGA9C50P3X3_144X144X62;DRV2605YZFR;;;;;Top;DRV2605YZFR;https://www.arrow.com/en/products/drv2605yzfr/texas-instrume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;;;;Haptic Driver for ERM/LRA with Built-In Library and Smart Loop Architecture;;Texas Instruments;DRV2605YZFR;;;;;;;;;;;;;
IC3;1;Accelerometers Triaxial low-g 12bit Acceleration Sensor;BMA423_BMA423;BMA421;;;;;Top;BMA423;https://www.arrow.com/en/products/bma423/bosch;;;;Accelerometers Triaxial low-g 12bit Acceleration Sensor;;BOSCH;BMA423;;;262-BMA423;https://www.mouser.co.uk/ProductDetail/Bosch-Sensortec/BMA42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;;;;;;;;;
IC9;1;Buck-Boost Regulator Positive Output Step-Up/Step-Down I2C DC-DC Controller IC 15-WL-CSP (BSC) (1.4x2.3);RT6160AWSC_BGA15C40P3X5_140X230X60;RT6160AWSC;;;;;Top;;;;;;Buck-Boost Regulator Positive Output Step-Up/Step-Down I2C DC-DC Controller IC 15-WL-CSP (BSC) (1.4x2.3);;RICHTEK;RT6160AWSC;;;835-RT6160AWSC;https://www.mouser.co.uk/ProductDetail/Richtek/RT6160AWSC?qs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;;;;;;;;;
J1;1;FFC & FPC Connectors 0.5mm FPC RA SMT Dual Contact 24Ckt;503480-2400_5034802400;503480-2400;;;;;Top;;;;;;FFC & FPC Connectors 0.5mm FPC RA SMT Dual Contact 24Ckt;;Molex;503480-2400;;;538-503480-2400;https://www.mouser.co.uk/ProductDetail/Molex/503480-2400?qs=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;;;;;;;;;
J2;1;CABLE ADAPTER 6 POS;TC2030-IDC_TC2030IDC;TC2030-IDC;;;;;Top;;;;;;CABLE ADAPTER 6 POS;;Tag Connect;TC2030-IDC;;;;;;;;;;;;;
J4;1;Check availability;KH-TYPE-C-16P_KINGHELM_KH-TYPE-C-16P;KH-TYPE-C-16P;;;;;Top;;;Not in stock;https://www.snapeda.com/parts/KH-TYPE-C-16P/Kinghelm/view-pa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;;                                                                                                    ;;;;kinghelm;;;;KH-TYPE-C-16P;None;;None;;;https://www.snapeda.com/parts/KH-TYPE-C-16P/Kinghelm/view-pa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;;
L1;1;Generic chip inductor;NORDIC_NRF_2_RESC0402_L;3.9nH;;;;;Top;;;;;;;;;;;;;;;;;;;;;;
L2;1;Generic chip inductor;NORDIC_NRF_2_RESC0603_L;10uH;;;;;Top;;;;;;;;;;;;;;;;;;;;;;
L3;1;Generic chip inductor;NORDIC_NRF_2_RESC0201_L;15nH;;;;;Top;;;;;;;;;;;;;;;;;;;;;;
L5;1;;ESP32_C6_LIBRARY_2_IND_4828-WE-TPC_WRE;68uH;;;;;Top;;;;;Copyright (C) 2024 Ultra Librarian. All rights reserved.;;;;744043680;;Wurth Electronics;;;;;;;;;;;
L7;1;SMD / SMT Inductors (Coils), L=0.47?H, L x W x T :;MLP2016SR47MT0S1_INDC2016X100N;FTC252012SR47MBCA;;;;;Top;;;;;;SMD / SMT Inductors (Coils), L=0.47?H, L x W x T :;https://jlcpcb.com/partdetail/6763488-FTC252012SR47MBCA/C5832368;TDK;FTC252012SR47MBCA;;;;;;;;;;;;;
Q1;1;P-channel MOSFETs;ESP32_WROVER_SPARKFUN-DISCRETESEMI_SOT23-3;20V/4.2A/52mΩ/1.4W;;;;;Top;;;;;;;;;;;;;;;;;;TRAN-14388;;;;
Q3;1;MOSFET N-Ch 30V 1.5A TrenchFET SC70 Vishay Si1308EDL-T1-GE3 N-channel MOSFET Transistor, 1.5 A, 30 V, 3-Pin SC-70;SOT65P210X110-3N;SI1308EDL-T1-GE3;;;;;Top;;;In Stock;https://www.snapeda.com/parts/SI1308EDL-T1-GE3/Vishay+Silico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;; Si1308EDL-T1-GE3 N-channel MOSFET Transistor, 1.5 A, 30 V, 3-Pin SC-70 | Siliconix / Vishay SI1308EDL-T1-GE3 ;;;;Vishay Siliconix;;;;SI1308EDL-T1-GE3;SOT-323 Vishay Semiconductor;;None;;https://www.snapeda.com/api/url_track_click_mouser/?unipart_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 Siliconix&part_name=SI1308EDL-T1-GE3&search_term=None;https://www.snapeda.com/parts/SI1308EDL-T1-GE3/Vishay+Silico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;;
R_PWR_EPD, R2_EP_DR, R9;3;7.68k 0201 Thin Film Surface Mount Fixed Resistor +/-0.5% 0.031W CPF0201D7K68C1;CPF0201D7K68C1_0201;10K;;;;;Top;;;;;;;;;;;;;;;;;;;;;;
R_TYPE_SEL;1;7.68k 0201 Thin Film Surface Mount Fixed Resistor +/-0.5% 0.031W CPF0201D7K68C1;CPF0201D7K68C1_0201;2.2;;;;;Top;;;;;;;;;;;;;;;;;;;;;;
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
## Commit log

2026-04-08 Add Apache License 2.0
    Added the Apache License 2.0 to the project.
2026-04-09 Before review
2026-04-10 Added 3D
2026-04-21 more views
2026-04-22 fixed readme

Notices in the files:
Manufacturing/billOfMaterials.csv:
3;;2025-10-22_07-23-44_LIBRARY_SW_EVP-AKE31A_PAN;2025-10-22_07-23-44_LIBRARY_EVP-AKE31ASW_EVP-AKE31A_PAN;;;;;Top;;;;;Copyright (C) 2025 Ultra Librarian. All rights reserved.;;;Panasonic;EVP-AKE31A;;;;;;;;;;;;;
parts and their libraries:
COPYRIGHT: Copyright (C) 2024 Ultra Librarian. All rights reserved.
COPYRIGHT: Copyright (C) 2025 Ultra Librarian. All rights reserved.
